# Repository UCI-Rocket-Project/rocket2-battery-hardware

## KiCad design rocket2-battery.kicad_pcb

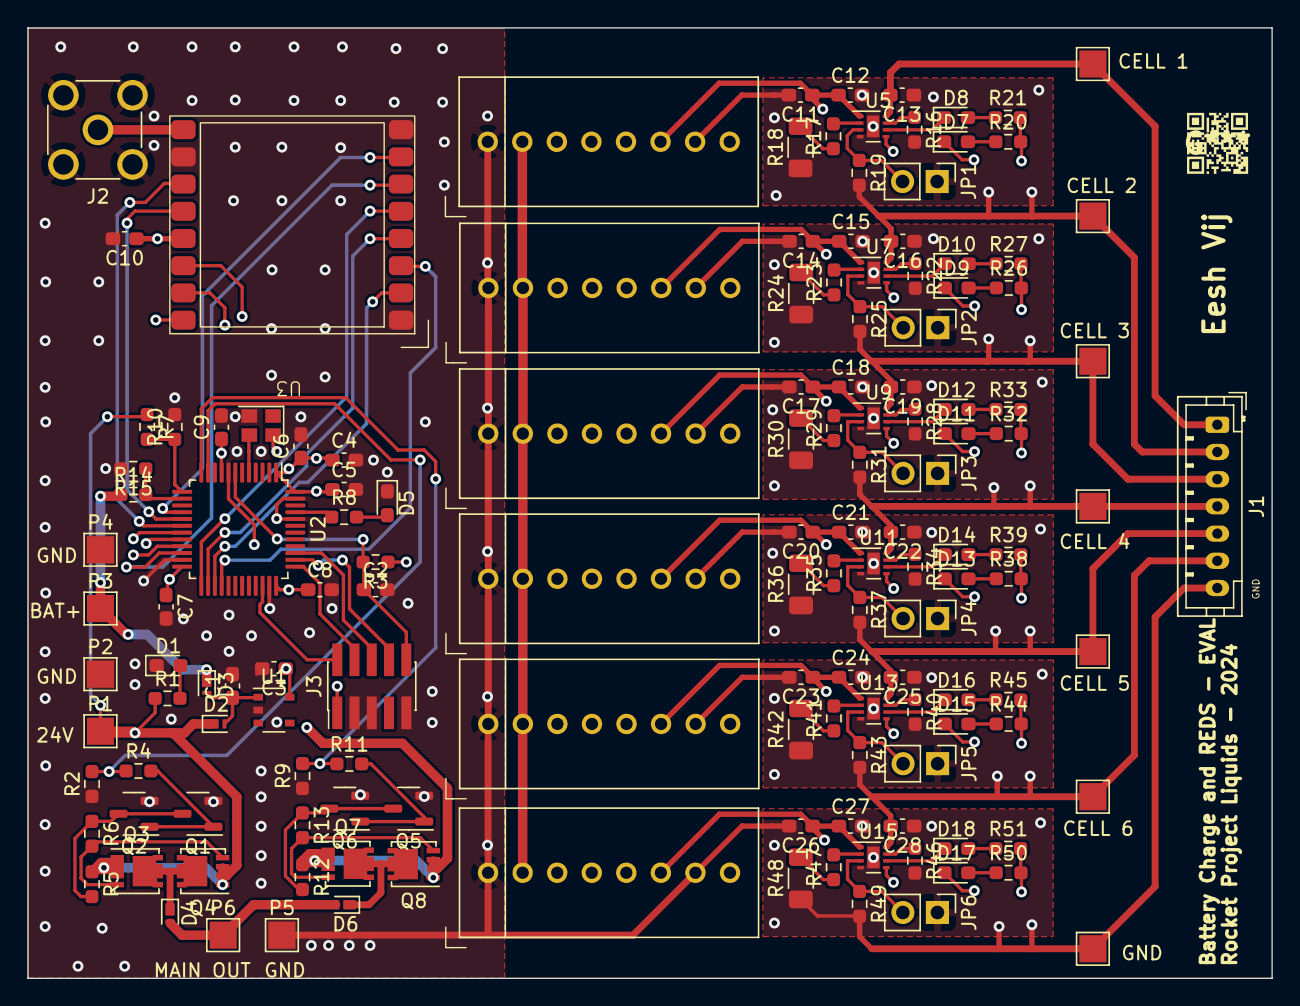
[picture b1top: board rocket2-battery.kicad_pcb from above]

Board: 4 copper layers, 91.4 x 69.8 mm, 143 parts (0 on the bottom side), 99 nets.

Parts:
C1, C3, C11, C13, C14, C16, C17, C19, C20, C22, C23, C25, C26, C28: 1uF; C_0603_1608Metric_Pad1.08x0.95mm_HandSolder
C2, C5, C6, C7, C8, C9: 100nF; C_0603_1608Metric_Pad1.08x0.95mm_HandSolder
C4: 4.7uF; C_0603_1608Metric_Pad1.08x0.95mm_HandSolder
C10, C12, C15, C18, C21, C24, C27: 10uF; C_0603_1608Metric_Pad1.08x0.95mm_HandSolder
D1: LED; LED_0603_1608Metric_Pad1.05x0.95mm_HandSolder
D2, D3, D4, D6: 30V 2A; Nexperia_DSN1608-2_1.6x0.8mm
D5: LED; D_0603_1608Metric_Pad1.05x0.95mm_HandSolder
D7, D9, D11, D13, D15, D17: BLUE_LED; LED_0603_1608Metric_Pad1.05x0.95mm_HandSolder
D8, D10, D12, D14, D16, D18: RED_LED; LED_0603_1608Metric_Pad1.05x0.95mm_HandSolder
J1: Conn_01x07; JST_PH_B7B-PH-K_1x07_P2.00mm_Vertical
J2: SMA; SMA_Molex_73251-2200_Horizontal
J3: ARM Cortex Debug; PinHeader_2x05_P1.27mm_Vertical_SMD
JP1, JP2, JP3, JP4, JP5, JP6: NO_Jump; PinHeader_1x02_P2.54mm_Vertical
P1, P2, P3, P4, P5, P6: PAD_SMD; TestPoint_Pad_2.0x2.0mm
Q1, Q2, Q5, Q6: Q_NMOS_GSD; SOT-23-3
Q3, Q4, Q7, Q8: PMOS; Vishay_PowerPAK_1212-8_Single
R1: 3.3k; R_0603_1608Metric_Pad0.98x0.95mm_HandSolder
R2, R8, R9: 1K; R_0603_1608Metric_Pad0.98x0.95mm_HandSolder
R3, R5, R12, R19, R20, R21, R25, R26, R27, R31, R32, R33, R37, R38, R39, R43, R44, R45, R49, R50, R51: 10K; R_0603_1608Metric_Pad0.98x0.95mm_HandSolder
R4, R6, R11, R13: 100; R_0603_1608Metric_Pad0.98x0.95mm_HandSolder
R7, R14: 100k; R_0603_1608Metric_Pad0.98x0.95mm_HandSolder
R10, R15: 15K; R_0603_1608Metric_Pad0.98x0.95mm_HandSolder
R16, R22, R28, R34, R40, R46: 27K; R_0603_1608Metric_Pad0.98x0.95mm_HandSolder
R17, R23, R29, R35, R41, R47: 375; R_0603_1608Metric_Pad0.98x0.95mm_HandSolder
R18, R24, R30, R36, R42, R48: 0; R_1206_3216Metric_Pad1.30x1.75mm_HandSolder
TP1: Cell 1; TestPoint_Pad_2.0x2.0mm
TP2: Cell 2; TestPoint_Pad_2.0x2.0mm
TP3: Cell 3; TestPoint_Pad_2.0x2.0mm
TP4: Cell 4; TestPoint_Pad_2.0x2.0mm
TP5: Cell 5; TestPoint_Pad_2.0x2.0mm
TP6: Cell 6; TestPoint_Pad_2.0x2.0mm
TP7: GND; TestPoint_Pad_2.0x2.0mm
U1: 3V3 LDO; TSOP-5_1.65x3.05mm_P0.95mm
U2: LQFP-48_7x7mm_P0.5mm
U3: RFM95W
U4, U6, U8, U10, U12, U14: EC4SAW-xxSxxN
U5, U7, U9, U11, U13, U15: WSON-8-1EP_2x2mm_P0.5mm_EP0.9x1.6mm
Y1: 16MHz; Crystal_SMD_2520-4Pin_2.5x2.0mm

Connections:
+3.3V: C3.1, C4.1, C5.1, C6.1, C7.1, C8.1, C9.1, C10.1, J3.1 (VCC), R3.1, U1.5 (OUT), U2.1 (VBAT), U2.9 (VDDA), U2.24 (VDD), U2.36 (VDD), U2.48 (VDD), U3.13 (3.3V), Y1.4
+24V: D2.1 (A), P1.1 (PAD), Q3.1 (S), Q3.2 (S), Q3.3 (S), Q4.1 (S), Q4.2 (S), Q4.3 (S), R1.1, R5.1, R7.1, U4.2 (VIN+), U6.2 (VIN+), U8.2 (VIN+), U10.2 (VIN+), U12.2 (VIN+), U14.2 (VIN+)
/BATT_MAIN+: D3.1 (A), P3.1 (PAD), Q7.1 (S), Q7.2 (S), Q7.3 (S), Q8.1 (S), Q8.2 (S), Q8.3 (S), R12.1, R14.1
/BAT_OUT+: C13.2, J1.1, TP1.1, U5.8 (OUT)
/MAIN+: D4.2 (K), D6.2 (K), P6.1 (PAD)
/Single-Cell-Charger1/ISO_5V: C14.1, C15.1, R26.2, R27.2, U6.6 (VOUT+), U7.1 (IN)
/Single-Cell-Charger1/ISO_GND: C14.2, C15.2, C16.1, C19.2, J1.3, JP2.1 (A), R22.2, R24.1, R25.2, TP3.1, U6.7 (VOUT-), U7.4 (GND), U7.9 (GND), U9.8 (OUT)
/Single-Cell-Charger2/ISO_5V: C17.1, C18.1, R32.2, R33.2, U8.6 (VOUT+), U9.1 (IN)
/Single-Cell-Charger2/ISO_GND: C17.2, C18.2, C19.1, C22.2, J1.4, JP3.1 (A), R28.2, R30.1, R31.2, TP4.1, U8.7 (VOUT-), U9.4 (GND), U9.9 (GND), U11.8 (OUT)
/Single-Cell-Charger3/ISO_5V: C20.1, C21.1, R38.2, R39.2, U10.6 (VOUT+), U11.1 (IN)
/Single-Cell-Charger3/ISO_GND: C20.2, C21.2, C22.1, C25.2, J1.5, JP4.1 (A), R34.2, R36.1, R37.2, TP5.1, U10.7 (VOUT-), U11.4 (GND), U11.9 (GND), U13.8 (OUT)
/Single-Cell-Charger4/ISO_5V: C23.1, C24.1, R44.2, R45.2, U12.6 (VOUT+), U13.1 (IN)
/Single-Cell-Charger4/ISO_GND: C23.2, C24.2, C25.1, C28.2, J1.6, JP5.1 (A), R40.2, R42.1, R43.2, TP6.1, U12.7 (VOUT-), U13.4 (GND), U13.9 (GND), U15.8 (OUT)
/Single-Cell-Charger5/ISO_5V: C26.1, C27.1, R50.2, R51.2, U14.6 (VOUT+), U15.1 (IN)
/Single-Cell-Charger/ISO_5V: C11.1, C12.1, R20.2, R21.2, U4.6 (VOUT+), U5.1 (IN)
/Single-Cell-Charger/ISO_GND: C11.2, C12.2, C13.1, C16.2, J1.2, JP1.1 (A), R16.2, R18.1, R19.2, TP2.1, U4.7 (VOUT-), U5.4 (GND), U5.9 (GND), U7.8 (OUT)
GND: C1.2, C2.2, C3.2, C4.2, C5.2, C6.2, C7.2, C8.2, C9.2, C10.2, C26.2, C27.2, C28.1, D1.1 (K), D5.1 (K), J1.7, J2.2 (Ext), J3.3 (GND), J3.5 (GND), J3.9 (GND_Detect), JP6.1 (A), P2.1 (PAD), P4.1 (PAD), P5.1 (PAD), Q1.2 (S), Q2.2 (S), Q5.2 (S), Q6.2 (S), R2.1, R9.1, R10.2, R15.2, R46.2, R48.1, R49.2, TP7.1, U1.2 (GND), U2.8 (VSSA), U2.23 (VSS), U2.35 (VSS), U2.44 (BOOT0), U2.47 (VSS), U3.1 (GND), U3.8 (GND), U3.10 (GND), U4.1 (VIN-), U6.1 (VIN-), U8.1 (VIN-), U10.1 (VIN-), U12.1 (VIN-), U14.1 (VIN-), U14.7 (VOUT-), U15.4 (GND), U15.9 (GND), Y1.2
MCU_TCK: J3.4 (SWDCLK/TCK), U2.37 (PA14)
MCU_TDI: J3.8 (NC/TDI), U2.38 (PA15)
MCU_TDO: J3.6 (SWO/TDO), U2.39 (PB3)
MCU_TMS: J3.2 (SWDIO/TMS), U2.34 (PA13)
MCU_~RST: C2.1, J3.10 (~RST), R3.2, U2.7 (~RST)
MOSFET1: R2.2, R4.1, U2.11 (PA1)
MOSFET2: R9.2, R11.1, U2.12 (PA2)
unnamed: D1.2 (A), R1.2
unnamed: C1.1, D2.2 (K), D3.2 (K), U1.1 (IN)
unnamed: D4.1 (A), Q3.5 (D), Q4.5 (D)
unnamed: D5.2 (A), R8.2
unnamed: D6.1 (A), Q7.5 (D), Q8.5 (D)
unnamed: D7.2 (A), R20.1
unnamed: D7.1 (K), U5.5 (STAT)
unnamed: D8.2 (A), R21.1
unnamed: D8.1 (K), U5.6 (~PG)
unnamed: D9.2 (A), R26.1
unnamed: D9.1 (K), U7.5 (STAT)
unnamed: D10.2 (A), R27.1
unnamed: D10.1 (K), U7.6 (~PG)
unnamed: D11.2 (A), R32.1
unnamed: D11.1 (K), U9.5 (STAT)
unnamed: D12.2 (A), R33.1
unnamed: D12.1 (K), U9.6 (~PG)
unnamed: D13.2 (A), R38.1
unnamed: D13.1 (K), U11.5 (STAT)
unnamed: D14.2 (A), R39.1
unnamed: D14.1 (K), U11.6 (~PG)
unnamed: D15.2 (A), R44.1
unnamed: D15.1 (K), U13.5 (STAT)
unnamed: D16.2 (A), R45.1
unnamed: D16.1 (K), U13.6 (~PG)
unnamed: D17.2 (A), R50.1
unnamed: D17.1 (K), U15.5 (STAT)
unnamed: D18.2 (A), R51.1
unnamed: D18.1 (K), U15.6 (~PG)
unnamed: J2.1 (In), U3.9 (ANT)
unnamed: JP1.2 (B), R19.1, U5.3 (TS)
unnamed: JP2.2 (B), R25.1, U7.3 (TS)
unnamed: JP3.2 (B), R31.1, U9.3 (TS)
unnamed: JP4.2 (B), R37.1, U11.3 (TS)
unnamed: JP5.2 (B), R43.1, U13.3 (TS)
unnamed: JP6.2 (B), R49.1, U15.3 (TS)
unnamed: Q1.3 (D), Q2.3 (D), R5.2, R6.1
unnamed: Q1.1 (G), Q2.1 (G), R4.2
unnamed: Q3.4 (G), Q4.4 (G), R6.2
unnamed: Q5.3 (D), Q6.3 (D), R12.2, R13.1
unnamed: Q5.1 (G), Q6.1 (G), R11.2
unnamed: Q7.4 (G), Q8.4 (G), R13.2
unnamed: R17.1, R18.2
unnamed: R23.1, R24.2
unnamed: R29.1, R30.2
unnamed: R35.1, R36.2
unnamed: R41.1, R42.2
unnamed: R47.1, R48.2
unnamed: R8.1, U2.45 (PB8)
unnamed: U2.5 (PD0), Y1.3
unnamed: R17.2, U5.2 (ISET)
unnamed: R16.1, U5.7 (VSET)
unnamed: R23.2, U7.2 (ISET)
unnamed: R22.1, U7.7 (VSET)
unnamed: R29.2, U9.2 (ISET)
unnamed: R28.1, U9.7 (VSET)
unnamed: R35.2, U11.2 (ISET)
unnamed: R34.1, U11.7 (VSET)
unnamed: R41.2, U13.2 (ISET)
unnamed: R40.1, U13.7 (VSET)
unnamed: R47.2, U15.2 (ISET)
unnamed: R46.1, U15.7 (VSET)
RADIO_DIO0: U2.21 (PB10), U3.14 (DIO0)
RADIO_DIO1: U2.20 (PB2), U3.15 (DIO1)
RADIO_DIO2: U2.19 (PB1), U3.16 (DIO2)
RADIO_DIO3: U2.18 (PB0), U3.11 (DIO3)
RADIO_DIO4: U2.17 (PA7), U3.12 (DIO4)
RADIO_DIO5: U2.16 (PA6), U3.7 (DIO5)
RADIO_MISO: U2.27 (PB14), U3.2 (MISO)
RADIO_MOSI: U2.28 (PB15), U3.3 (MOSI)
RADIO_SCK: U2.26 (PB13), U3.4 (SCK)
RADIO_nCS: U2.25 (PB12), U3.5 (~CS)
RADIO_nRST: U2.22 (PB11), U3.6 (~RST)
V_SENSE1: R7.2, R10.1, U2.13 (PA3)
V_SENSE2: R14.2, R15.1, U2.14 (PA4)

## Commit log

2024-01-31 Initalized repo
2024-02-01 added symbol for batt IC
2024-02-01 Basic schematic
2024-02-01 added isolated 5v
2024-02-02 turned into heirarchical
2024-02-03 finished schematic; (major parts selected)
2024-02-07 Updated schematic with symbols and footprints
2024-02-07 Almost done with REDs
2024-02-08 Finished Schematic; Time to Review
2024-02-08 Fixed issues
2024-02-09 Made Charging layout
2024-02-09 Squished
2024-02-09 mosfets done
2024-02-09 Almost done routing
2024-02-09 Finished most of layout
2024-02-09 Finished; Passed DRC
2024-02-10 Daniel suggestions; Fixed charger part
2024-02-10 Finished
2024-02-10 some more minor fixes
2024-02-15 Changed PMOS
2024-02-18 some minor fixes
2024-03-20 Fix diode footprints & other things I don't remember
2024-03-23 fixed nmos
